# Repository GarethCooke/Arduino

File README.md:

# Arduino

Arduino, ESP8266, and ESP32 projects.

## Standalone projects

Complete systems with their own repos, docs, and release history:

| Project | Description | Docs |
| ------- | ----------- | ---- |
| [MorayGlow](https://github.com/GarethCooke/MorayGlow) | WiFi RGB LED strip controller — XIAO ESP32-S3, custom PCB, MQTT/REST/WebSocket, Home Assistant | [garethcooke.github.io/MorayGlow](https://garethcooke.github.io/MorayGlow/) |
| [WhisperBridge](https://github.com/GarethCooke/WhisperBridge) | WiFi/MQTT-to-BLE bridge for Vent-Axia Svara fan, Home Assistant integration, no cloud required | [garethcooke.github.io/WhisperBridge](https://garethcooke.github.io/WhisperBridge/) |

## Experiments and prototypes

Smaller, exploratory projects that live here:

- **BeatReceiveTest** / **BeatReceiveWifi** — beat detection and WiFi sync experiments
- **EqualiserTest** — audio equaliser prototype
- **LEDStrip** — early LED strip work (preceded MorayGlow)
- **VentAxia** — Vent-Axia fan analysis (preceded WhisperBridge)

## Common libraries

Shared code used across projects lives in [`Common/`](Common/):

- **IguanaLib** — core utilities
- **IguanaFont** — font rendering helpers
- **IguanaBeat** — beat detection library

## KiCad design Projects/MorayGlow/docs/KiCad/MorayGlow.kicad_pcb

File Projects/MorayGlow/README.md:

# MorrayGlow

IoT LED strip controller — ESP8266 firmware + web UI with Home Assistant integration.

## Project Summary

MorrayGlow controls an RGB LED strip via a **Wemos D1 mini (ESP8266)**. The device hosts a web UI and exposes a REST + WebSocket API. A browser-based client lets you toggle the strip on/off and pick a colour. The device also integrates with **Home Assistant** via MQTT auto-discovery, so it appears automatically as a light entity.

## Project Structure

```text
MorayGlow/
├── MorrayServer/               # ESP8266 firmware (C++, PlatformIO)
│   ├── platformio.ini
│   ├── src/main.cpp            # WiFi, LittleFS, REST API, WebSocket
│   ├── include/
│   │   ├── config.h            # WiFi credentials, MQTT config — edit before flashing
│   │   ├── state.h             # Pure logic: stateToJson, rgbToHex, parseMqttCommand
│   │   └── mqtt.h              # MQTT client + Home Assistant discovery
│   └── test/
│       └── test_state.cpp      # Unity tests (run on host, not device)
└── MorrayClient/               # Web UI (plain HTML/CSS/JS — no framework)
    ├── index.html
    ├── css/style.css
    ├── js/
    │   ├── morray.js           # UMD utility module (buildWsUrl, isValidHexColor)
    │   └── app.js              # Main UI logic
    ├── test/
    │   └── morray.test.js      # Jest tests for morray.js
    └── test-server/            # Node.js mock server for UI development
        ├── server.js
        ├── logic.js            # Pure functions (testable without starting server)
        ├── db.json             # Persisted state between restarts
        └── test/
            └── server.test.js  # Jest tests for logic.js
```

## API

| Method | Endpoint       | Body                    | Description                                   |
| ------ | -------------- | ----------------------- | --------------------------------------------- |
| GET    | `/api/state`   | —                       | Returns `{"on": bool, "color": "#rrggbb"}`    |
| POST   | `/api/power`   | `{"on": bool}`          | Turn strip on or off                          |
| POST   | `/api/color`   | `{"color": "#rrggbb"}`  | Set strip colour                              |
| WS     | `/ws`          | —                       | Server pushes state on every change           |

## Design Decisions

| Decision       | Choice                                          | Reason                                                  |
| -------------- | ----------------------------------------------- | ------------------------------------------------------- |
| MCU            | Wemos D1 mini (ESP8266)                         | Small, cheap, Wi-Fi built in                            |
| Build system   | PlatformIO                                      | Dependency management, board config, native test env    |
| Web server     | `esphome/ESPAsyncWebServer-esphome`             | Supports ESP8266 + ESP32; async                         |
| Filesystem     | LittleFS                                        | Serves client files from device flash                   |
| JSON           | ArduinoJson v7 (`JsonDocument`)                 | No capacity arg needed; widely supported                |
| MQTT           | `knolleary/PubSubClient` + `setBufferSize(512)` | Lightweight, well-maintained                            |
| HA integration | MQTT auto-discovery                             | Device appears automatically in Home Assistant          |
| Client         | Plain HTML/CSS/JS (no framework)                | Keeps LittleFS footprint small                          |
| Client module  | UMD pattern (`morray.js`)                       | Works as browser global and Node.js/Jest module         |
| Testability    | Pure functions in `state.h` / `logic.js`        | Compiled and tested on host without hardware            |
| C++ tests      | Unity (via PlatformIO native env)               | Bundled with PlatformIO; runs on host                   |
| JS tests       | Jest                                            | Standard, zero-config for CommonJS modules              |

## Before Flashing

Edit `MorrayServer/include/config.h` and set your WiFi SSID/password and MQTT broker IP before building and flashing.

## Running Tests

### MorrayServer — C++ firmware (Unity via PlatformIO)

Requires `gcc`/`g++` on your PATH (install MinGW-w64 if not present).

```powershell
cd MorrayServer
pio test -e native
```

### MorrayClient — browser JS logic (Jest)

```powershell
cd MorrayClient
npm install   # first time only
npm test
```

### Test server — Node.js logic (Jest)

```powershell
cd MorrayClient\test-server
npm install   # first time only
npm test
```

---

## Starting the Test Server

The test server lets you develop and test the web UI without the physical device.

```powershell
cd MorrayClient\test-server
npm install   # first time only
npm start
```

Then open [http://localhost:3000](http://localhost:3000) in a browser.

State is persisted to `MorrayClient\test-server\db.json` between restarts.

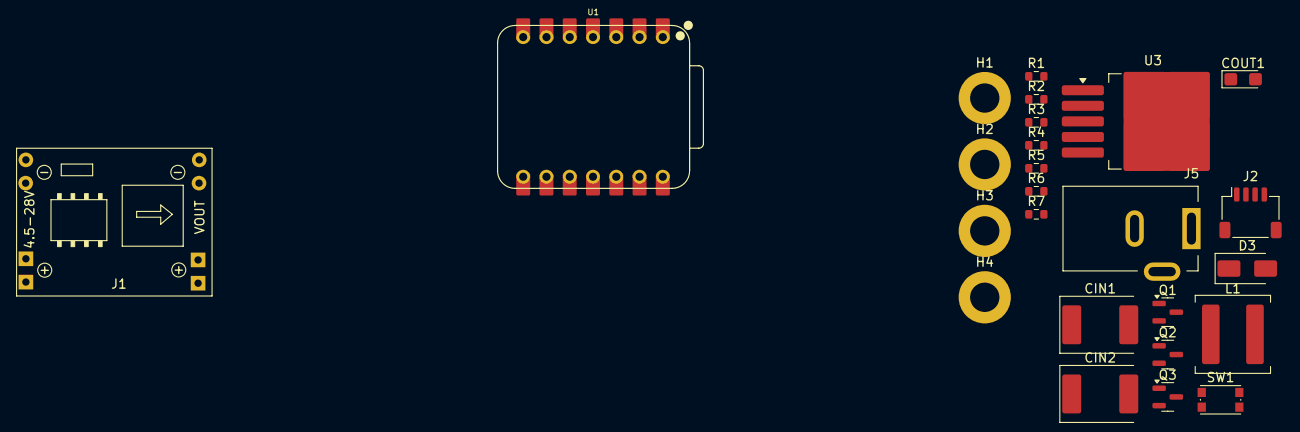
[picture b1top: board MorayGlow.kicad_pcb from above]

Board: 2 copper layers, 25 parts (0 on the bottom side), 17 nets, no tracks yet.

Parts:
CIN1, CIN2: 330uF; CP_EIA-7360-38_Kemet-E
COUT1: 220uF; CP_EIA-3216-18_Kemet-A
D3: SK32; D_SMA
H1, H2, H3, H4: Hole_Pad; MountingHole_3.2mm_M3_ISO7380_Pad
J1: Conn_01x04; SRT_MPT1584EN_Module
J2: RGB LED; JST_SH_SM04B-SRSS-TB_1x04-1MP_P1.00mm_Horizontal
J5: Barrel Jack; BarrelJack_Kycon_KLDX-0202-xC_Horizontal
L1: 3uH; L_Coilcraft_XAL7070-XXX
Q1, Q2, Q3: IRFML8244; SOT-23
R1, R2, R3: 100; R_0603_1608Metric
R4, R5, R6: 10k; R_0603_1608Metric
R7: 330; R_0603_1608Metric
SW1: SW_DIP_x01; SW_Push_1P1T_NO_CK_KMR2
U1: XIAO-ESP32-S3-Plus-SMD; XIAO-ESP32-S3-DIP
U3: LM2596S-5; TO-263-5_TabPin3

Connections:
<NO NET>: CIN1.2, CIN2.2, COUT1.2, D3.2 (A), H1.1, H2.1, H3.1, H4.1, J5.3, R4.2, R5.2, R6.2, SW1.1, U1.13 (GND), U3.3 (GND), U3.5 (~ON/OFF)
CMD_BTN: SW1.2, U1.5 (GPIO5_A4_D4_SDA)
LED_B: J2.4, Q3.1 (D)
LED_G: J2.2, Q2.1 (D)
LED_R: J2.3, Q1.1 (D)
unnamed: D3.1 (K), L1.1, U3.2 (OUT)
unnamed: Q1.2 (G), R1.1
unnamed: Q1.3 (S), R4.1
unnamed: Q2.2 (G), R2.1
unnamed: Q2.3 (S), R5.1
unnamed: Q3.2 (G), R3.1
unnamed: Q3.3 (S), R6.1
RGB_B: R3.2, U1.3 (GPIO3_A2_D2)
RGB_G: R2.2, U1.2 (GPIO2_A1_D1)
RGB_R: R1.2, U1.1 (GPIO1_A0_D0)
VCC_12V: CIN1.1, CIN2.1, J2.1, J5.1, U3.1 (VIN)
VDD_5V: COUT1.1, L1.2, U1.14 (VBUS), U3.4 (FB)

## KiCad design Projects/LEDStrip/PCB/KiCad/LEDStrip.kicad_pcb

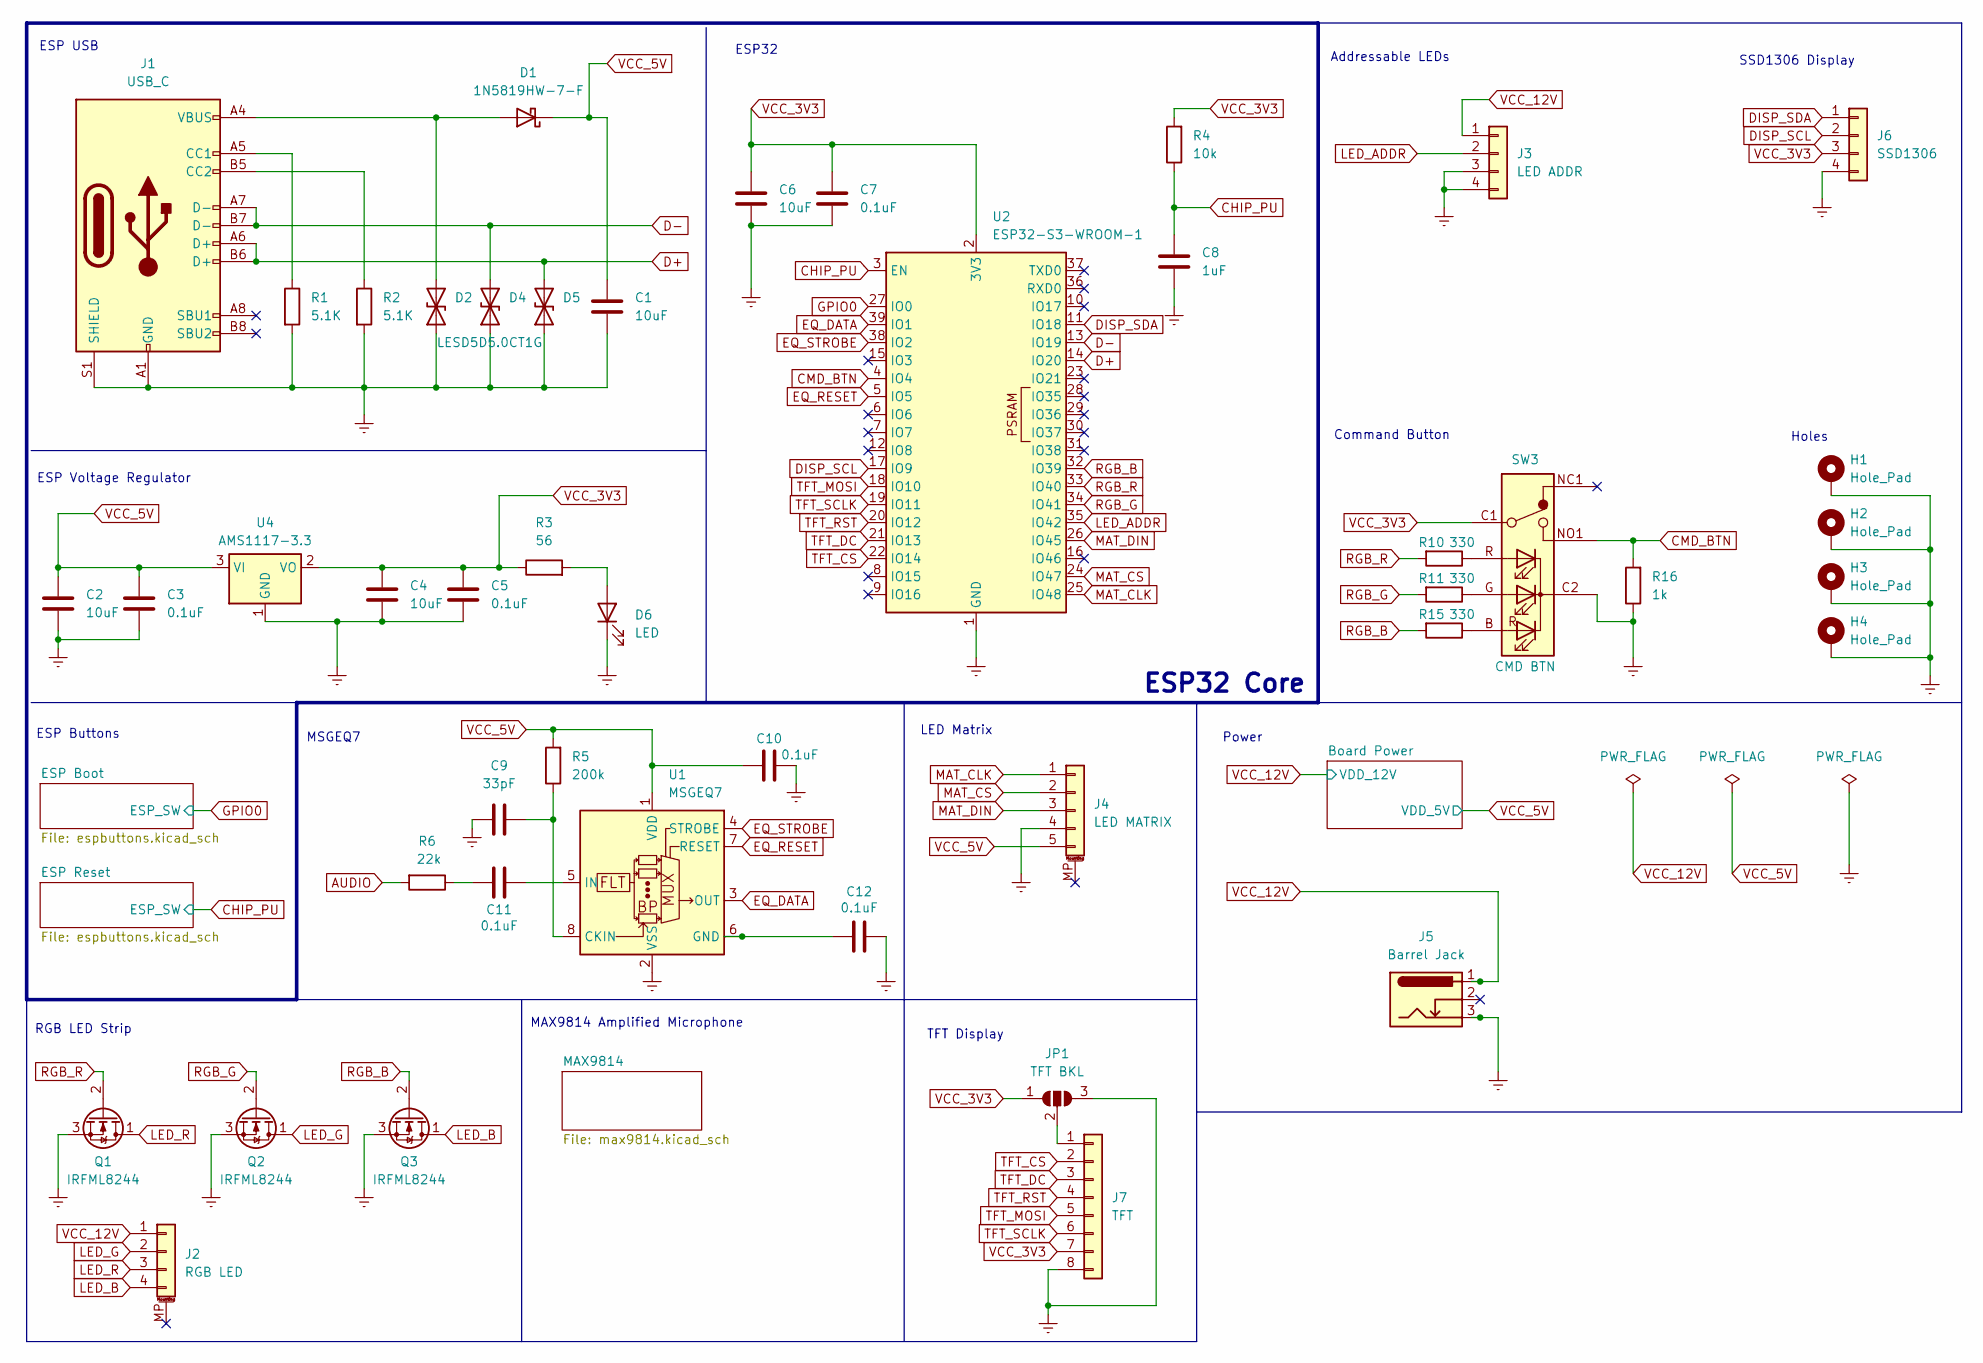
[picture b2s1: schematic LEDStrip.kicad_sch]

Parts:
C1, C2, C4, C6: 10uF; C_0603_1608Metric
C3, C5, C7, C10, C11, C12: 0.1uF; C_0603_1608Metric
C8: 1uF; C_0603_1608Metric
C9: 33pF; C_0603_1608Metric
D1: 1N5819HW-7-F; D_SOD-123
D2, D4, D5: LESD5D5.0CT1G; D_SOD-523
D6: LED; LED_0603_1608Metric
H1, H2, H3, H4: Hole_Pad; MountingHole_3.2mm_M3_ISO7380_Pad
J1: USB_C; USB_C_Receptacle_Palconn_UTC16-G
J2: RGB LED; JST_SH_SM04B-SRSS-TB_1x04-1MP_P1.00mm_Horizontal
J3: LED ADDR; JST_EH_S4B-EH_1x04_P2.50mm_Horizontal
J4: LED MATRIX; JST_SH_SM05B-SRSS-TB_1x05-1MP_P1.00mm_Horizontal
J5: Barrel Jack; BarrelJack_Kycon_KLDX-0202-xC_Horizontal
J6: SSD1306; PinHeader_1x04_P2.54mm_Vertical
J7: TFT; PinHeader_1x08_P2.54mm_Vertical
JP1: TFT BKL; SolderJumper-3_P1.3mm_Open_RoundedPad1.0x1.5mm_NumberLabels
Q1, Q2, Q3: IRFML8244; SOT-23
R1, R2: 5.1K; R_0603_1608Metric
R3: 56; R_0603_1608Metric
R4: 10k; R_0603_1608Metric
R5: 200k; R_0603_1608Metric
R6: 22k; R_0603_1608Metric
R10, R11, R15: 330; R_0603_1608Metric
R16: 1k; R_0603_1608Metric
SW3: CMD BTN; SW_RGB_JST_SH
U1: MSGEQ7; DIP-8_W7.62mm_Socket
U2: ESP32-S3-WROOM-1
U4: AMS1117-3.3; SOT-223-3_TabPin2

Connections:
AUDIO: R6.2; also elsewhere on the board
CHIP_PU: C8.1, R4.1, U2.3 (EN); also elsewhere on the board
CMD_BTN: R16.2, SW3.NO1, U2.4 (IO4)
D+: D5.2 (A2), J1.A6 (D+), J1.B6 (D+), U2.14 (IO20)
D-: D4.2 (A2), J1.A7 (D-), J1.B7 (D-), U2.13 (IO19)
DISP_SCL: J6.2, U2.17 (IO9)
DISP_SDA: J6.1, U2.11 (IO18)
EQ_DATA: U1.3 (OUT), U2.39 (IO1)
EQ_RESET: U1.7 (RESET), U2.5 (IO5)
EQ_STROBE: U1.4 (STROBE), U2.38 (IO2)
ESP_3V3: C4.1, C5.1, C6.1, C7.1, J6.3, J7.7, JP1.1 (A), R3.1, R4.2, SW3.C1, U2.2 (3V3), U4.2 (VO); also elsewhere on the board
GND: C1.2, C2.2, C3.2, C4.2, C5.2, C6.2, C7.2, C8.2, C9.1, C10.2, C12.2, D2.1 (A1), D4.1 (A1), D5.1 (A1), D6.1 (K), H1.1, H2.1, H3.1, H4.1, J1.A1 (GND), J1.A12 (GND), J1.B1 (GND), J1.B12 (GND), J1.S1 (SHIELD), J3.3, J3.4, J4.4, J5.3, J6.4, J7.8, JP1.3 (B), Q1.3 (S), Q2.3 (S), Q3.3 (S), R1.2, R2.2, R16.1, SW3.C2, U1.2 (VSS), U2.1 (GND), U2.40 (GND), U2.41 (GND), U4.1 (GND)
GPIO0: U2.27 (IO0); also elsewhere on the board
LED_ADDR: J3.2, U2.35 (IO42)
LED_B: J2.4, Q3.1 (D)
LED_G: J2.2, Q2.1 (D)
LED_R: J2.3, Q1.1 (D)
MAT_CLK: J4.1, U2.25 (IO48)
MAT_CS: J4.2, U2.24 (IO47)
MAT_DIN: J4.3, U2.26 (IO45)
unnamed: C11.1, R6.1
unnamed: D1.2 (A), D2.2 (A2), J1.A4 (VBUS), J1.A9 (VBUS), J1.B4 (VBUS), J1.B9 (VBUS)
unnamed: D6.2 (A), R3.2
unnamed: J1.A5 (CC1), R1.1
unnamed: J1.B5 (CC2), R2.1
unnamed: J7.1, JP1.2 (C)
unnamed: R10.1, SW3.R
unnamed: R11.1, SW3.G
unnamed: R15.1, SW3.B
unnamed: C9.2, R5.1, U1.8 (CKIN)
unnamed: C12.1, U1.6 (GND)
unnamed: C11.2, U1.5 (IN)
RGB_B: Q3.2 (G), R15.2, U2.32 (IO39)
RGB_G: Q2.2 (G), R11.2, U2.34 (IO41)
RGB_R: Q1.2 (G), R10.2, U2.33 (IO40)
TFT_CS: J7.2, U2.22 (IO14)
TFT_DC: J7.3, U2.21 (IO13)
TFT_MOSI: J7.5, U2.18 (IO10)
TFT_RST: J7.4, U2.20 (IO12)
TFT_SCLK: J7.6, U2.19 (IO11)
VCC_12V: J2.1, J3.1, J5.1; also elsewhere on the board

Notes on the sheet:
SSD1306 Display
ESP32 Core
Power
MAX9814 Amplified Microphone
Command Button
ESP32
RGB LED Strip
LED Matrix
Holes
Addressable LEDs
ESP USB
MSGEQ7
ESP Buttons
ESP Voltage Regulator
TFT Display

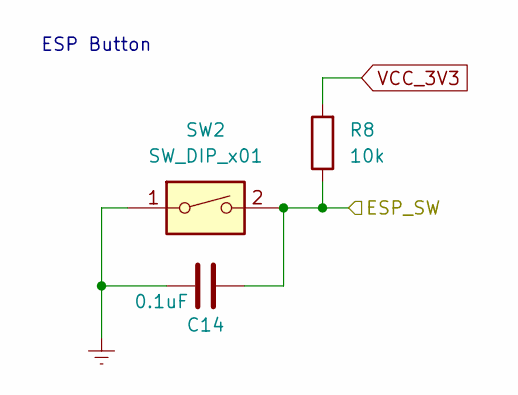
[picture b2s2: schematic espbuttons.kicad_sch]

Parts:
C14: 0.1uF; C_0603_1608Metric
R8: 10k; R_0603_1608Metric
SW2: SW_DIP_x01; SW_Push_1P1T_NO_CK_KMR2

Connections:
<NO NET>: C14.2, SW2.1; also elsewhere on the board
ESP_3V3: R8.2; also elsewhere on the board
GPIO0: C14.1, R8.1, SW2.2; also elsewhere on the board

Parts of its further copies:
C13: 0.1uF; C_0603_1608Metric
R7: 10k; R_0603_1608Metric

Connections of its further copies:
<NO NET>: C13.2; also elsewhere on the board
CHIP_PU: C13.1, R7.1; also elsewhere on the board
ESP_3V3: R7.2; also elsewhere on the board

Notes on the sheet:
ESP Button

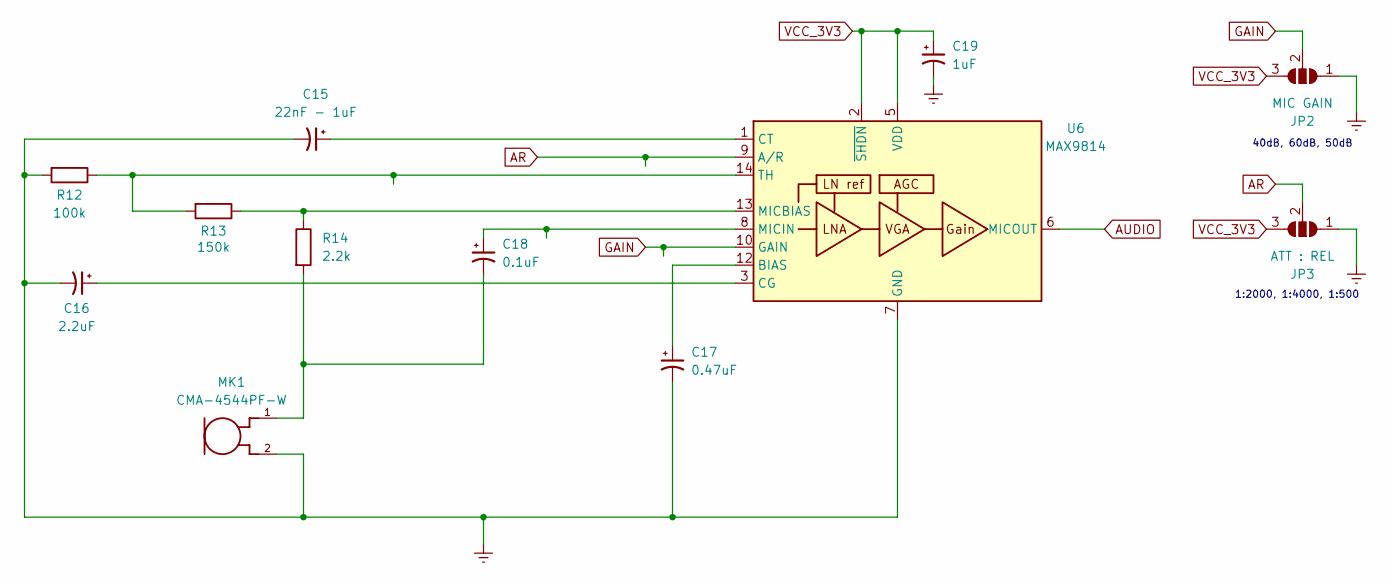
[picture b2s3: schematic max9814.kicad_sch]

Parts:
C15: 22nF - 1uF; CP_EIA-3216-18_Kemet-A
C16: 2.2uF; CP_EIA-3216-18_Kemet-A
C17: 0.47uF; CP_EIA-3216-18_Kemet-A
C18: 0.1uF; CP_EIA-3216-18_Kemet-A
C19: 1uF; CP_EIA-3216-18_Kemet-A
JP2: MIC GAIN; SolderJumper-3_P1.3mm_Open_RoundedPad1.0x1.5mm_NumberLabels
JP3: ATT : REL; SolderJumper-3_P1.3mm_Open_RoundedPad1.0x1.5mm_NumberLabels
MK1: CMA-4544PF-W; MIC_CMA-4544PF-W
R12: 100k; R_0603_1608Metric
R13: 150k; R_0603_1608Metric
R14: 2.2k; R_0603_1608Metric
U6: MAX9814; DFN-14-1EP_3x3mm_P0.4mm_EP1.78x2.35mm

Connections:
<NO NET>: C15.2, C16.2, C17.2, C19.2, JP2.1 (A), JP3.1 (A), MK1.2, R12.2, U6.4 (GND), U6.7 (GND), U6.11 (GND), U6.15 (GND); also elsewhere on the board
AR: JP3.2 (C), U6.9 (A/R)
AUDIO: U6.6 (MICOUT); also elsewhere on the board
ESP_3V3: C19.1, JP2.3 (B), JP3.3 (B), U6.2 (~SHDN), U6.5 (VDD); also elsewhere on the board
GAIN: JP2.2 (C), U6.10 (GAIN)
unnamed: C18.2, MK1.1, R14.2
unnamed: C17.1, U6.12 (BIAS)
unnamed: C16.1, U6.3 (CG)
unnamed: C15.1, U6.1 (CT)
unnamed: R13.1, R14.1, U6.13 (MICBIAS)
unnamed: C18.1, U6.8 (MICIN)
unnamed: R12.1, R13.2, U6.14 (TH)

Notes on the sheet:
40dB, 60dB, 50dB
1:2000, 1:4000, 1:500

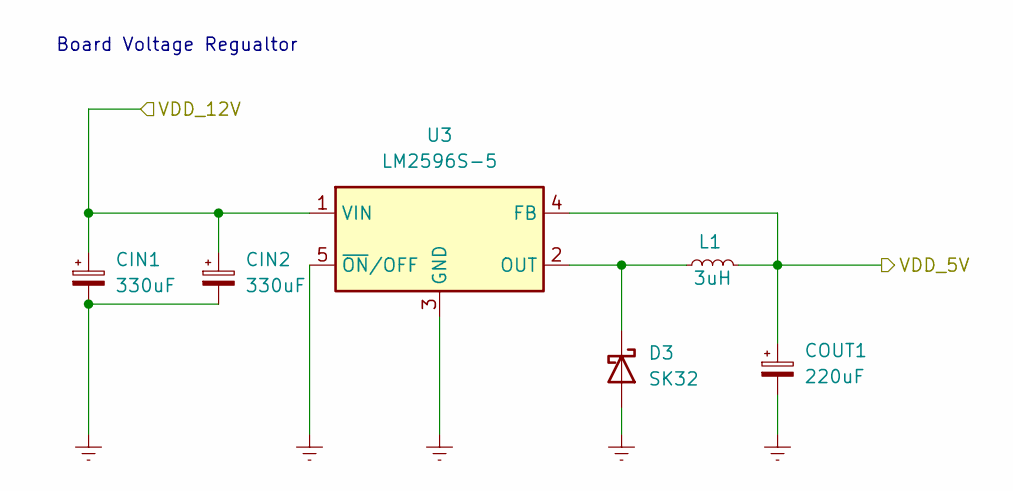
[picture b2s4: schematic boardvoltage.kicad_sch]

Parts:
CIN1, CIN2: 330uF; CP_EIA-7360-38_Kemet-E
COUT1: 220uF; CP_EIA-3216-18_Kemet-A
D3: SK32; D_SMA
L1: 3uH; L_Coilcraft_XAL7070-XXX
U3: LM2596S-5; TO-263-5_TabPin3

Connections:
<NO NET>: CIN1.2, CIN2.2, COUT1.2, D3.2 (A), U3.3 (GND), U3.5 (~ON/OFF); also elsewhere on the board
unnamed: D3.1 (K), L1.1, U3.2 (OUT)
VCC_12V: CIN1.1, CIN2.1, U3.1 (VIN); also elsewhere on the board

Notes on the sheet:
Board Voltage Regualtor

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
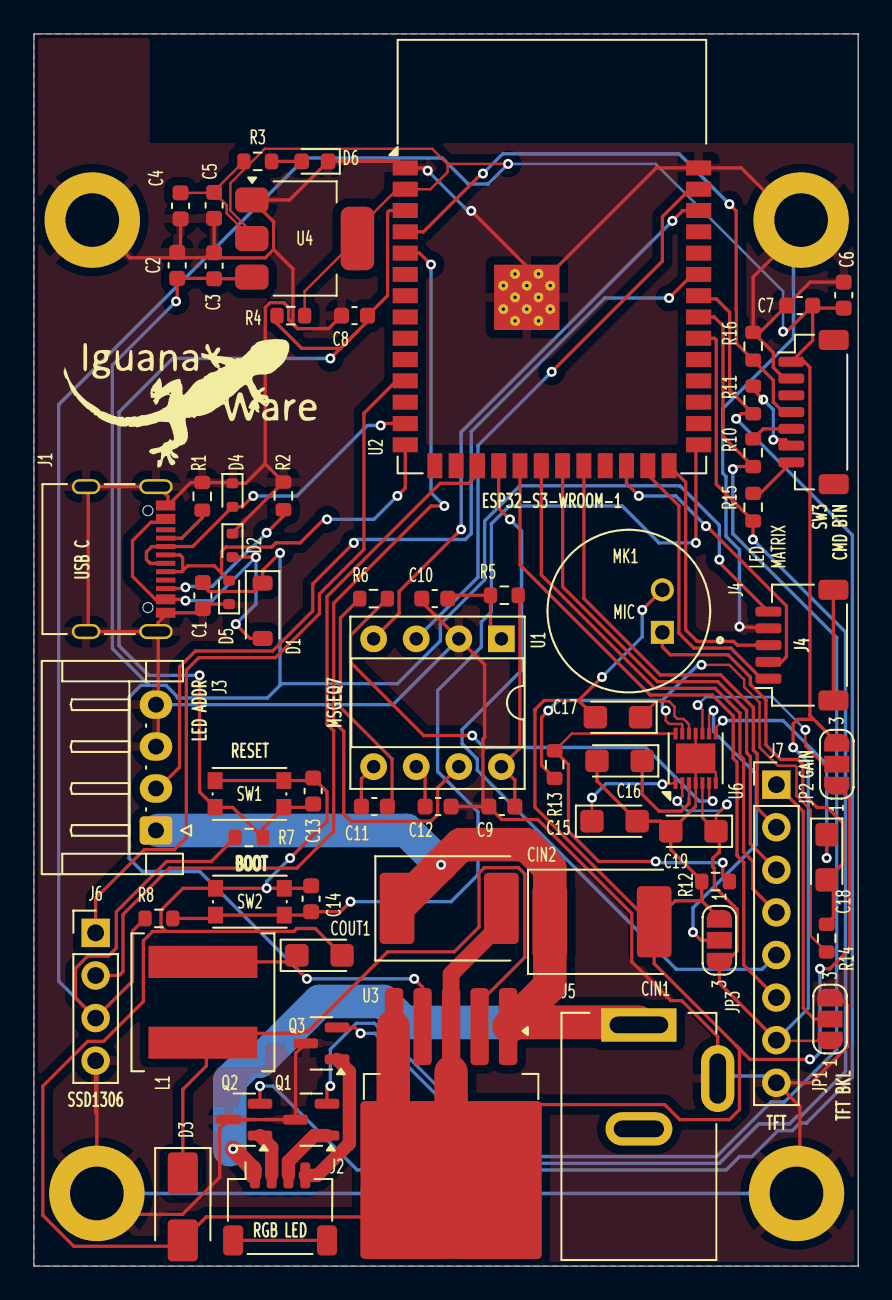
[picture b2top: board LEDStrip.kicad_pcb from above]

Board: 2 copper layers, 49.2 x 73.5 mm, 70 parts (0 on the bottom side), 54 nets.

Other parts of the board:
SW1: RESET; SW_Push_1P1T_NO_CK_KMR2

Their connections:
<NO NET>: SW1.1; also elsewhere on the board
CHIP_PU: SW1.2; also elsewhere on the board

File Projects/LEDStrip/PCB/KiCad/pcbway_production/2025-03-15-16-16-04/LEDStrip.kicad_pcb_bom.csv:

Designator,Quantity,Value,Footprint,Package,MPN,DNP,Mount_Type,Description,MF,DESCRIPTION,PRICE,Check_prices,CUI_PURCHASE_URL,SnapEDA_Link,MP,Purchase-URL,Price,Availability,CUI_purchase_URL,AVAILABILITY,Description_1
"C1, C2, C4, C6",4,10uF,C_0603_1608Metric,,,,smt,Unpolarized capacitor,,,,,,,,,,,,,
"C10, C11, C12, C13, C14, C3, C5, C7",8,0.1uF,C_0603_1608Metric,,,,smt,Unpolarized capacitor,,,,,,,,,,,,,
C15,1,22nF - 1uF,CP_EIA-3216-18_Kemet-A,,,,smt,"Polarized capacitor, small US symbol",,,,,,,,,,,,,
C16,1,2.2uF,CP_EIA-3216-18_Kemet-A,,,,smt,"Polarized capacitor, small US symbol",,,,,,,,,,,,,
C17,1,0.47uF,CP_EIA-3216-18_Kemet-A,,,,smt,"Polarized capacitor, small US symbol",,,,,,,,,,,,,
C18,1,0.1uF,CP_EIA-3216-18_Kemet-A,,,,smt,"Polarized capacitor, small US symbol",,,,,,,,,,,,,
C19,1,1uF,CP_EIA-3216-18_Kemet-A,,,,smt,"Polarized capacitor, small US symbol",,,,,,,,,,,,,
C8,1,1uF,C_0603_1608Metric,,,,smt,Unpolarized capacitor,,,,,,,,,,,,,
C9,1,33pF,C_0603_1608Metric,,,,smt,Unpolarized capacitor,,,,,,,,,,,,,
"CIN1, CIN2",2,330uF,CP_EIA-7360-38_Kemet-E,,,,smt,"Polarized capacitor, small symbol",,,,,,,,,,,,,
COUT1,1,220uF,CP_EIA-3216-18_Kemet-A,,,,smt,"Polarized capacitor, small symbol",,,,,,,,,,,,,
D1,1,1N5819HW-7-F,D_SOD-123,,,,smt,Schottky diode,,,,,,,,,,,,,
"D2, D4, D5",3,LESD5D5.0CT1G,D_SOD-523,,,,smt,Bidirectional transient-voltage-suppression diode,,,,,,,,,,,,,
D3,1,SK32,D_SMA,,,,smt,Schottky diode,,,,,,,,,,,,,
D6,1,LED,LED_0603_1608Metric,,,,smt,Light emitting diode,,,,,,,,,,,,,
J1,1,USB C,USB_C_Receptacle_Palconn_UTC16-G,,,,smt,USB 2.0-only 16P Type-C Receptacle connector,,,,,,,,,,,,,
J2,1,RGB LED,JST_SH_SM04B-SRSS-TB_1x04-1MP_P1.00mm_Horizontal,,,,smt,"Generic connectable mounting pin connector, single row, 01x04, script generated (kicad-library-utils/schlib/autogen/connector/)",,,,,,,,,,,,,
J3,1,LED ADDR,JST_EH_S4B-EH_1x04_P2.50mm_Horizontal,,,,tht,"Generic connector, single row, 01x04, script generated (kicad-library-utils/schlib/autogen/connector/)",,,,,,,,,,,,,
J4,1,LED MATRIX,JST_SH_SM05B-SRSS-TB_1x05-1MP_P1.00mm_Horizontal,,,,smt,"Generic connectable mounting pin connector, single row, 01x05, script generated (kicad-library-utils/schlib/autogen/connector/)",,,,,,,,,,,,,
J5,1,Barrel Jack,BarrelJack_Kycon_KLDX-0202-xC_Horizontal,,,,tht,DC Barrel Jack with an internal switch,,,,,,,,,,,,,
J6,1,SSD1306,PinHeader_1x04_P2.54mm_Vertical,,,,tht,"Generic connector, single row, 01x04, script generated (kicad-library-utils/schlib/autogen/connector/)",,,,,,,,,,,,,
J7,1,TFT,PinHeader_1x08_P2.54mm_Vertical,,,,tht,"Generic connector, single row, 01x08, script generated (kicad-library-utils/schlib/autogen/connector/)",,,,,,,,,,,,,
L1,1,3uH,L_Coilcraft_XAL7070-XXX,,,,smt,"Inductor, small symbol",,,,,,,,,,,,,
MK1,1,CMA-4544PF-W,MIC_CMA-4544PF-W,6-DIP-6 CUI,,,tht,,CUI Devices,"9.7 mm, Omnidirectional, PCB Mount, 3.0 Vdc, Electret Condenser Microphone",None,https://www.snapeda.com/parts/CMA-4544PF-W/CUI+Devices/view-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,https://www.cui.com/product/audio/microphones/electret-conde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,https://www.snapeda.com/parts/CMA-4544PF-W/CUI+Devices/view-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,CMA-4544PF-W,https://www.snapeda.com/api/url_track_click_mouser/?unipart_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 Devices&part_name=CMA-4544PF-W&search_term=cma-4544pf,None,In Stock,https://www.cuidevices.com/product/audio/microphones/electre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,Unavailable,"9.7 mm, Omnidirectional, PCB Mount, 3.0 Vdc, Electret Condenser Microphone"
"Q1, Q2, Q3",3,IRFML8244,SOT-23,,,,smt,"14.4A Id, 100V Vds, 62mOhm Rds, N-Channel MOSFET, DirectFET SB",,,,,,,,,,,,,
"R1, R2",2,5.1K,R_0603_1608Metric,,,,smt,Resistor,,,,,,,,,,,,,
"R10, R11, R15",3,330,R_0603_1608Metric,,,,smt,Resistor,,,,,,,,,,,,,
R12,1,100k,R_0603_1608Metric,,,,smt,Resistor,,,,,,,,,,,,,
R13,1,150k,R_0603_1608Metric,,,,smt,Resistor,,,,,,,,,,,,,
R14,1,2.2k,R_0603_1608Metric,,,,smt,Resistor,,,,,,,,,,,,,
R16,1,1k,R_0603_1608Metric,,,,smt,Resistor,,,,,,,,,,,,,
R3,1,56,R_0603_1608Metric,,,,smt,Resistor,,,,,,,,,,,,,
"R4, R7, R8",3,10k,R_0603_1608Metric,,,,smt,Resistor,,,,,,,,,,,,,
R5,1,200k,R_0603_1608Metric,,,,smt,Resistor,,,,,,,,,,,,,
R6,1,22k,R_0603_1608Metric,,,,smt,Resistor,,,,,,,,,,,,,
SW1,1,RESET,SW_Push_1P1T_NO_CK_KMR2,,,,smt,"1x DIP Switch, Single Pole Single Throw (SPST) switch, small symbol",,,,,,,,,,,,,
SW2,1,SW_DIP_x01,SW_Push_1P1T_NO_CK_KMR2,,,,smt,"1x DIP Switch, Single Pole Single Throw (SPST) switch, small symbol",,,,,,,,,,,,,
SW3,1,CMD BTN,SW_RGB_JST_SH,,,,smt,,,,,,,,,,,,,,
U1,1,MSGEQ7,DIP-8_W7.62mm_Socket,,,,tht,"Seven Band Graphic Equalizer, DIP-8/SOIC-8",,,,,,,,,,,,,
U2,1,ESP32-S3-WROOM-1,ESP32-S3-WROOM-1,,,,smt,"RF Module, ESP32-S3 SoC, Wi-Fi 802.11b/g/n, Bluetooth, BLE, 32-bit, 3.3V, onboard antenna, SMD",,,,,,,,,,,,,
U3,1,LM2596S-5,TO-263-5_TabPin3,,,,smt,"5V 3A Step-Down Voltage Regulator, TO-263",,,,,,,,,,,,,
U4,1,AMS1117-3.3,SOT-223-3_TabPin2,,,,smt,"1A Low Dropout regulator, positive, 3.3V fixed output, SOT-223",,,,,,,,,,,,,
U6,1,MAX9814,DFN-14-1EP_3x3mm_P0.4mm_EP1.78x2.35mm,,,,smt,"Microphone Amplifier with AGC and Low-Noise Microphone Bias, TDFN-14",,,,,,,,,,,,,

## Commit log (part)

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2022-04-07 moved from private repository
2023-12-29 Vent Axia initial analysis
2023-12-29 new file, minor change
2023-12-29 upgraded dev tools - arduino (2.x), visual studio (2022) and visual micro (for vs2022)
2023-12-29 code to display host, mac and ip addresses on BeatDisplay screen.
2024-01-01 implemented addressable W2812B LED RGB strip
2024-01-01 parallel processing for hardware and events to free up web server processing
2024-01-06 housekeeping
2024-01-13 upgrading to ESP32 S3
2024-01-14 esp32 s3 changes
2024-01-14 Update LEDStrip.fzz
    esp32 s3 changes
2024-01-21 refactoring
2024-01-21 initial changes, still broken with stl issues for atmega
2024-01-22 changes to support other boards
2024-01-26 changes to help find equalizer noise
2024-02-09 changed beat recognition algorithm
2024-02-10 moved to vscode and platformio, changed beat detection mechanism
2024-02-10 different way to get beats., not convinced its better than prev approach
2024-02-17 completed rebuild
2024-02-18 i2c coms for MSGRQ7 output between two devices working
2024-02-18 basic UDP setup
2024-02-22 threaded i2c writing
2024-02-22 udp receive start
2024-03-16 Added TFT Display skeleton
2024-03-16 started PCB and Schematic layout
2024-03-17 changes for PCB
2024-03-22 Completed PCB design
2024-03-23 refactoring for BeatTFT
2024-03-24 changes in support of BeatDisplay refactoring
2024-04-12 SPIFFS -> LittleFS
2024-04-12 reverted to previous version (as it was when PCB completed) just in case
2024-04-26 kicad design
2024-04-28 core esp32 sections complete
2024-05-05 PCB Kicad
2024-05-05 tidy up pin nos
2024-05-14 pcb changes
2024-05-28 PCB changes - almost complete, still needs copper fill
2024-06-04 pcb final
2024-07-09 checks and finishing
2024-07-09 changes and finishing
2025-03-15 upgraded kicad to version 9.0
2025-03-15 removed bottom layer copper pour
    Removed bottom layer copper fill because I think this is why solder wasn't melting when using heat plate.
2025-03-22 completed analysis
2025-04-03 interim
2025-04-16 Rename main.cpp to LEDStrip.ino
2025-04-16 moved LEDStrip.ino up one directory to better support vsmicro
2025-04-18 Update .gitignore
    removed vstudio LEDStrip ignores
2025-04-27 Revert "moved LEDStrip.ino up one directory to better support vsmicro"
    This reverts commit 964f1b9736b563240f803525fb4d81beb357a5f5.
2025-04-27 Revert "Rename main.cpp to LEDStrip.ino"
    This reverts commit 5abdb0368059a4765516c387515d7d69b7135121.
2025-04-27 changes for debugging using platformio
2025-04-27 Reapply "Rename main.cpp to LEDStrip.ino"
    This reverts commit 853aab31a4d5f58800a3d83fd2b394808ac08d88.
2025-04-27 Reapply "moved LEDStrip.ino up one directory to better support vsmicro"
    This reverts commit 51f40180bf8c11bf5e1f22fe71a6274b06577c23.
2025-08-06 solution changes
2026-02-18 "Claude PR Assistant workflow"
2026-02-18 "Claude Code Review workflow"
2026-03-28 updated schmatic and pcb
2026-03-31 added optional status LED and updated documentation
2026-04-05 minor kicad
2026-04-05 added claude init file
